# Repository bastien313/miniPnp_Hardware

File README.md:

# miniPnp_Hardware
hardware of mini PNP

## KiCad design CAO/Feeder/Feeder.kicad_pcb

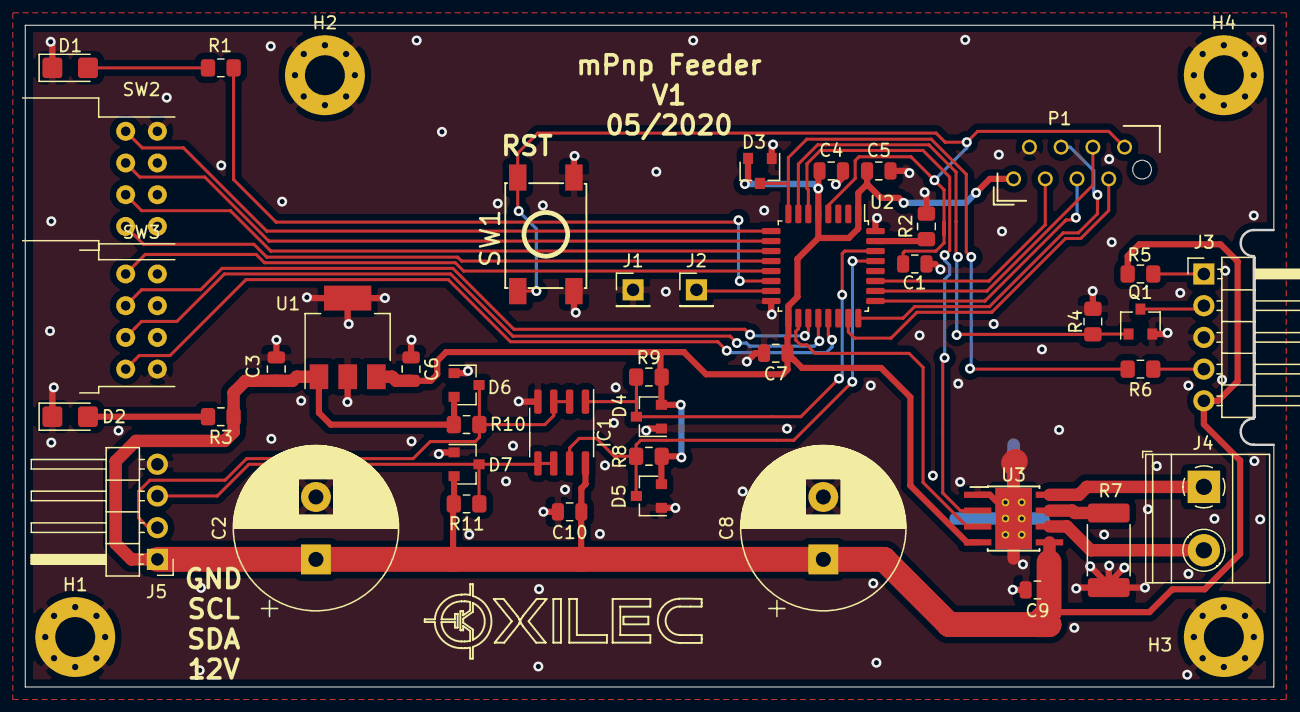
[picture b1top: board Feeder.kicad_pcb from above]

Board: 2 copper layers, 99.9 x 52.9 mm, 46 parts (0 on the bottom side), 36 nets.

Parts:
C1, C4, C5, C9, C10: 100nF; C_0805_2012Metric
C2, C8: 470uF 50V; CP_Radial_D13.0mm_P5.00mm
C3, C6: 330n 25V; C_0805_2012Metric
C7: 4.7uF 25V; C_0805_2012Metric
D1, D2: LED; LED_1206_3216Metric_Castellated
D3, D4, D5, D6, D7: BAT54S; SOT-23
H1, H2, H3, H4: MountingHole_Pad; MountingHole_3.2mm_M3_Pad_Via
IC1: PCA9600; SOIC-8_3.9x4.9mm_P1.27mm
J1, J2: Conn_01x01; PinHeader_1x01_P2.54mm_Vertical
J3: Conn_01x05; PinHeader_1x05_P2.54mm_Horizontal
J4: Born2; TerminalBlock_Phoenix_MKDS-1,5-2-5.08_1x02_P5.08mm_Horizont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
J5: Conn_01x04; PinHeader_1x04_P2.54mm_Horizontal
P1: CONN_4X2; 8Micro-MaTch
Q1: BSS138; SOT-23
R1, R3, R5, R8, R9, R10, R11: 1K; R_0805_2012Metric_Pad1.15x1.40mm_HandSolder
R2, R4: 100K; R_0805_2012Metric_Pad1.15x1.40mm_HandSolder
R6: 10k; R_0805_2012Metric_Pad1.15x1.40mm_HandSolder
R7: 0R; R_2512_6332Metric_Pad1.52x3.35mm_HandSolder
SW1: SW_Push; FSM2JSMA
SW2, SW3: SW_DIP_x04; DIPSW_4_COUDE
U1: MC33275ST-3.3T3G; SOT-223-3_TabPin2
U2: STM32F334K8Tx; LQFP-32_7x7mm_P0.8mm
U3: DRV8870DDA; Texas_HTSOP-8-1EP_3.9x4.9mm_P1.27mm_EP2.95x4.9mm_Mask2.4x3.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

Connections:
+3.3V: C4.1, C5.1, C6.2, C7.1, D3.2, D4.2, D5.2, P1.1, R8.1, R9.1, U1.3, U2.1, U2.5, U2.17, U3.4
+12V: C2.1, C3.2, C8.1, C9.1, C10.1, D6.2, D7.2, IC1.8, J3.5, J5.1, R3.1, R5.2, R10.1, R11.1, U1.1, U3.5
/ADR0: SW2.1, U2.9
/ADR1: SW2.2, U2.10
/ADR2: SW2.3, U2.11
/ADR3: SW2.4, U2.12
/ADR4: SW3.1, U2.13
/DC1: U2.18, U3.3
/DC2: U2.6, U3.2
/LEDIR_M: Q1.1, R4.2, U2.7
/NRST: C1.1, P1.8, SW1.1, U2.4
/SCL: D5.3, IC1.7, R8.2, U2.29
/SDA: D4.3, IC1.1, R9.2, U2.30
/TCK_SWCLK: P1.4, U2.24
/TDI: P1.5, U2.25
/TDO_SWO: P1.6, U2.26
/TIM15_CH1: D3.3, R6.2, U2.8
/TMS_SWDIO: P1.7, U2.23
/TRST: P1.3, U2.27
GND: C1.2, C2.2, C3.1, C4.2, C5.2, C6.1, C7.2, C8.2, C9.2, C10.2, D1.1, D2.1, D3.1, D4.1, D5.1, D6.1, D7.1, H1.1, H2.1, H3.1, H4.1, IC1.4, J1.1, J3.3, J5.4, P1.2, Q1.2, R2.2, R4.1, R7.2, SW1.2, SW2.5, SW2.6, SW2.7, SW2.8, SW3.5, SW3.6, SW3.7, SW3.8, U1.2, U2.16, U2.32, U3.1, U3.9
unnamed: D1.2, R1.2
unnamed: D2.2, R3.2
unnamed: D6.3, IC1.2, IC1.3, J5.2, R10.2
unnamed: D7.3, IC1.5, IC1.6, J5.3, R11.2
unnamed: J2.1, U2.15
unnamed: J3.1, R5.1
unnamed: J3.2, Q1.3
unnamed: J3.4, R6.1
unnamed: J4.1, U3.8
unnamed: J4.2, U3.6
unnamed: R1.1, U2.14
unnamed: R2.1, U2.31
unnamed: R7.1, U3.7
unnamed: SW3.2, U2.19
unnamed: SW3.3, U2.20
unnamed: SW3.4, U2.21

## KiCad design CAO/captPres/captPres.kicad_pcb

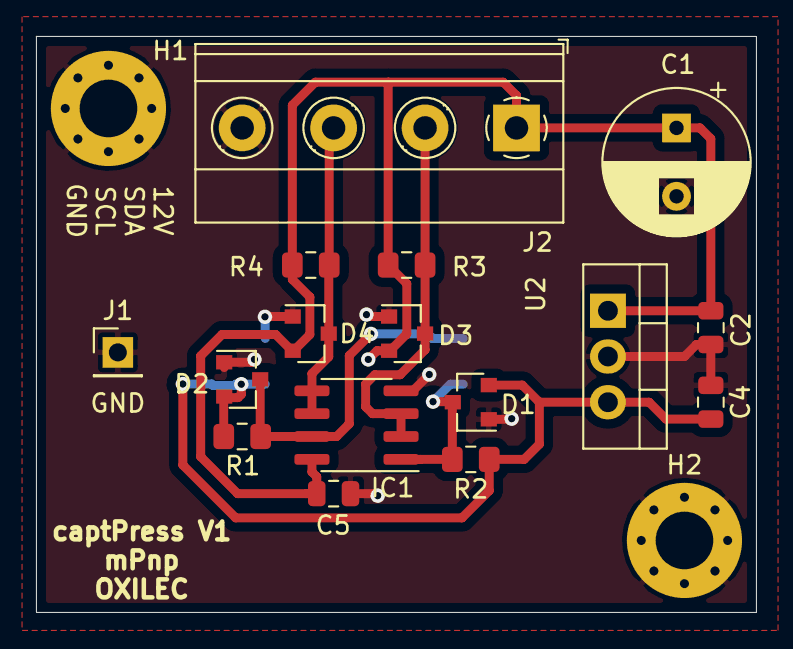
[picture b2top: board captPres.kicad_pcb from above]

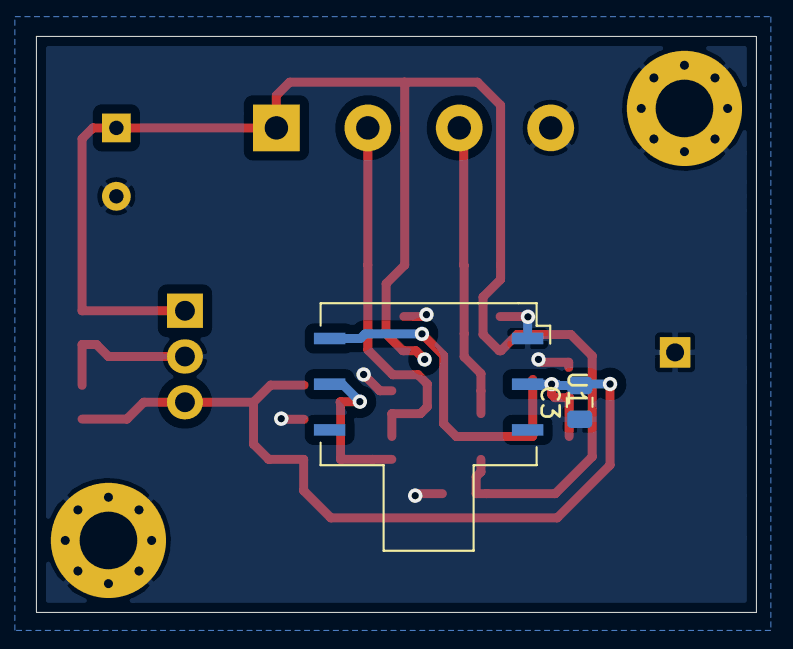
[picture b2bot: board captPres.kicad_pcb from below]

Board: 2 copper layers, 40.0 x 32.0 mm, 20 parts (2 on the bottom side), 7 nets.

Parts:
C1: CP1; CP_Radial_D8.0mm_P3.80mm
C2, C3, C5: 100nF; C_0805_2012Metric
C4: 2.2uF; C_0805_2012Metric
D1, D2, D3, D4: BAT54S; SOT-23
H1, H2: MountingHole_Pad; MountingHole_3.2mm_M3_Pad_Via
IC1: PCA9600; SOIC-8_3.9x4.9mm_P1.27mm
J1: Conn_01x01; PinHeader_1x01_P2.54mm_Vertical
J2: Conn_01x04; TerminalBlock_Phoenix_MKDS-1,5-4-5.08_1x04_P5.08mm_Horizont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
R1, R2, R3, R4: 1K; R_0805_2012Metric_Pad1.15x1.40mm_HandSolder
U1: ABPMRRV015PD2A3
U2: LF33_TO220; TO-220-3_Vertical

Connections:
+3V3USB: C3.2, C4.2, D1.2, D2.2, R1.1, R2.1, U1.2, U2.3
+12V: C1.1, C2.2, C5.1, D3.2, D4.2, IC1.8, J2.1, R3.1, R4.1, U2.1
/I2C/SCL: D2.3, IC1.7, R1.2, U1.6
/I2C/SDA: D1.3, IC1.1, R2.2, U1.5
GND: C1.2, C2.1, C3.1, C4.1, C5.2, D1.1, D2.1, D3.1, D4.1, H1.1, H2.1, IC1.4, J1.1, J2.4, U1.1, U2.2
unnamed: D3.3, IC1.2, IC1.3, J2.2, R3.2
unnamed: D4.3, IC1.5, IC1.6, J2.3, R4.2

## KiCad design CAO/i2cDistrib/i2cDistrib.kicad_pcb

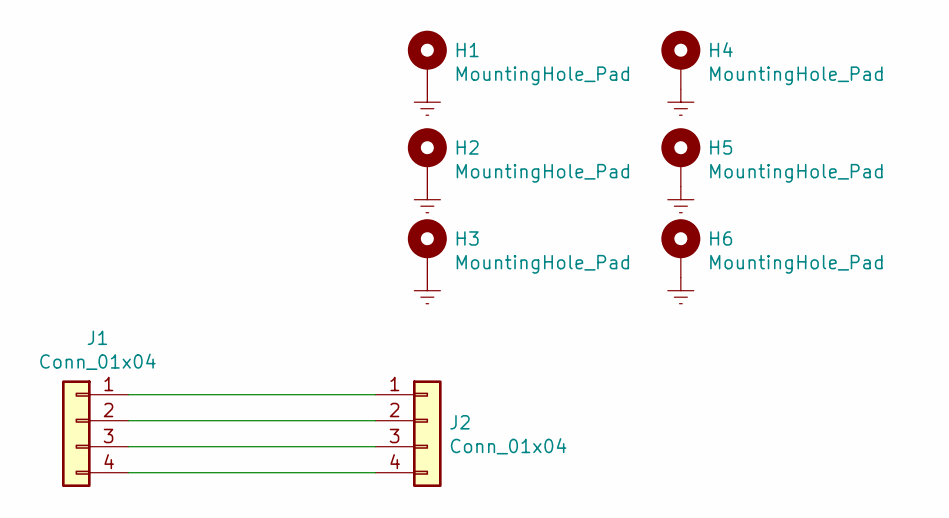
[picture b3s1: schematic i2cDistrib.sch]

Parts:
H1, H2, H3, H4, H5, H6: MountingHole_Pad; MountingHole_3mm_Pad_Via
J1, J2: Conn_01x04; Molex_KK-254_AE-6410-04A_1x04_P2.54mm_Vertical

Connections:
Earth: H1.1, H2.1, H3.1, H4.1, H5.1, H6.1
unnamed: J1.1, J2.1
unnamed: J1.2, J2.2
unnamed: J1.3, J2.3
unnamed: J1.4, J2.4

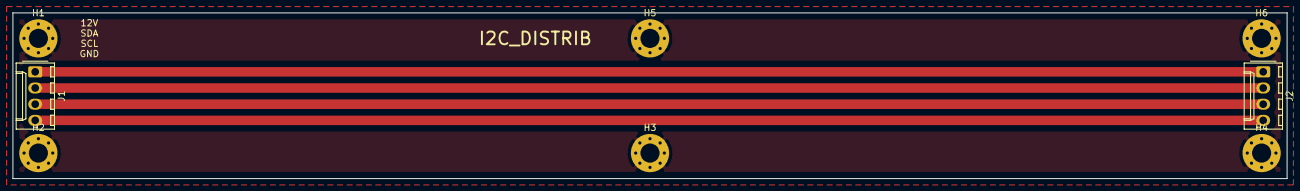
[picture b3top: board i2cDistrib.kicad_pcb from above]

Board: 2 copper layers, 200.0 x 26.0 mm, 8 parts (0 on the bottom side), 5 nets.

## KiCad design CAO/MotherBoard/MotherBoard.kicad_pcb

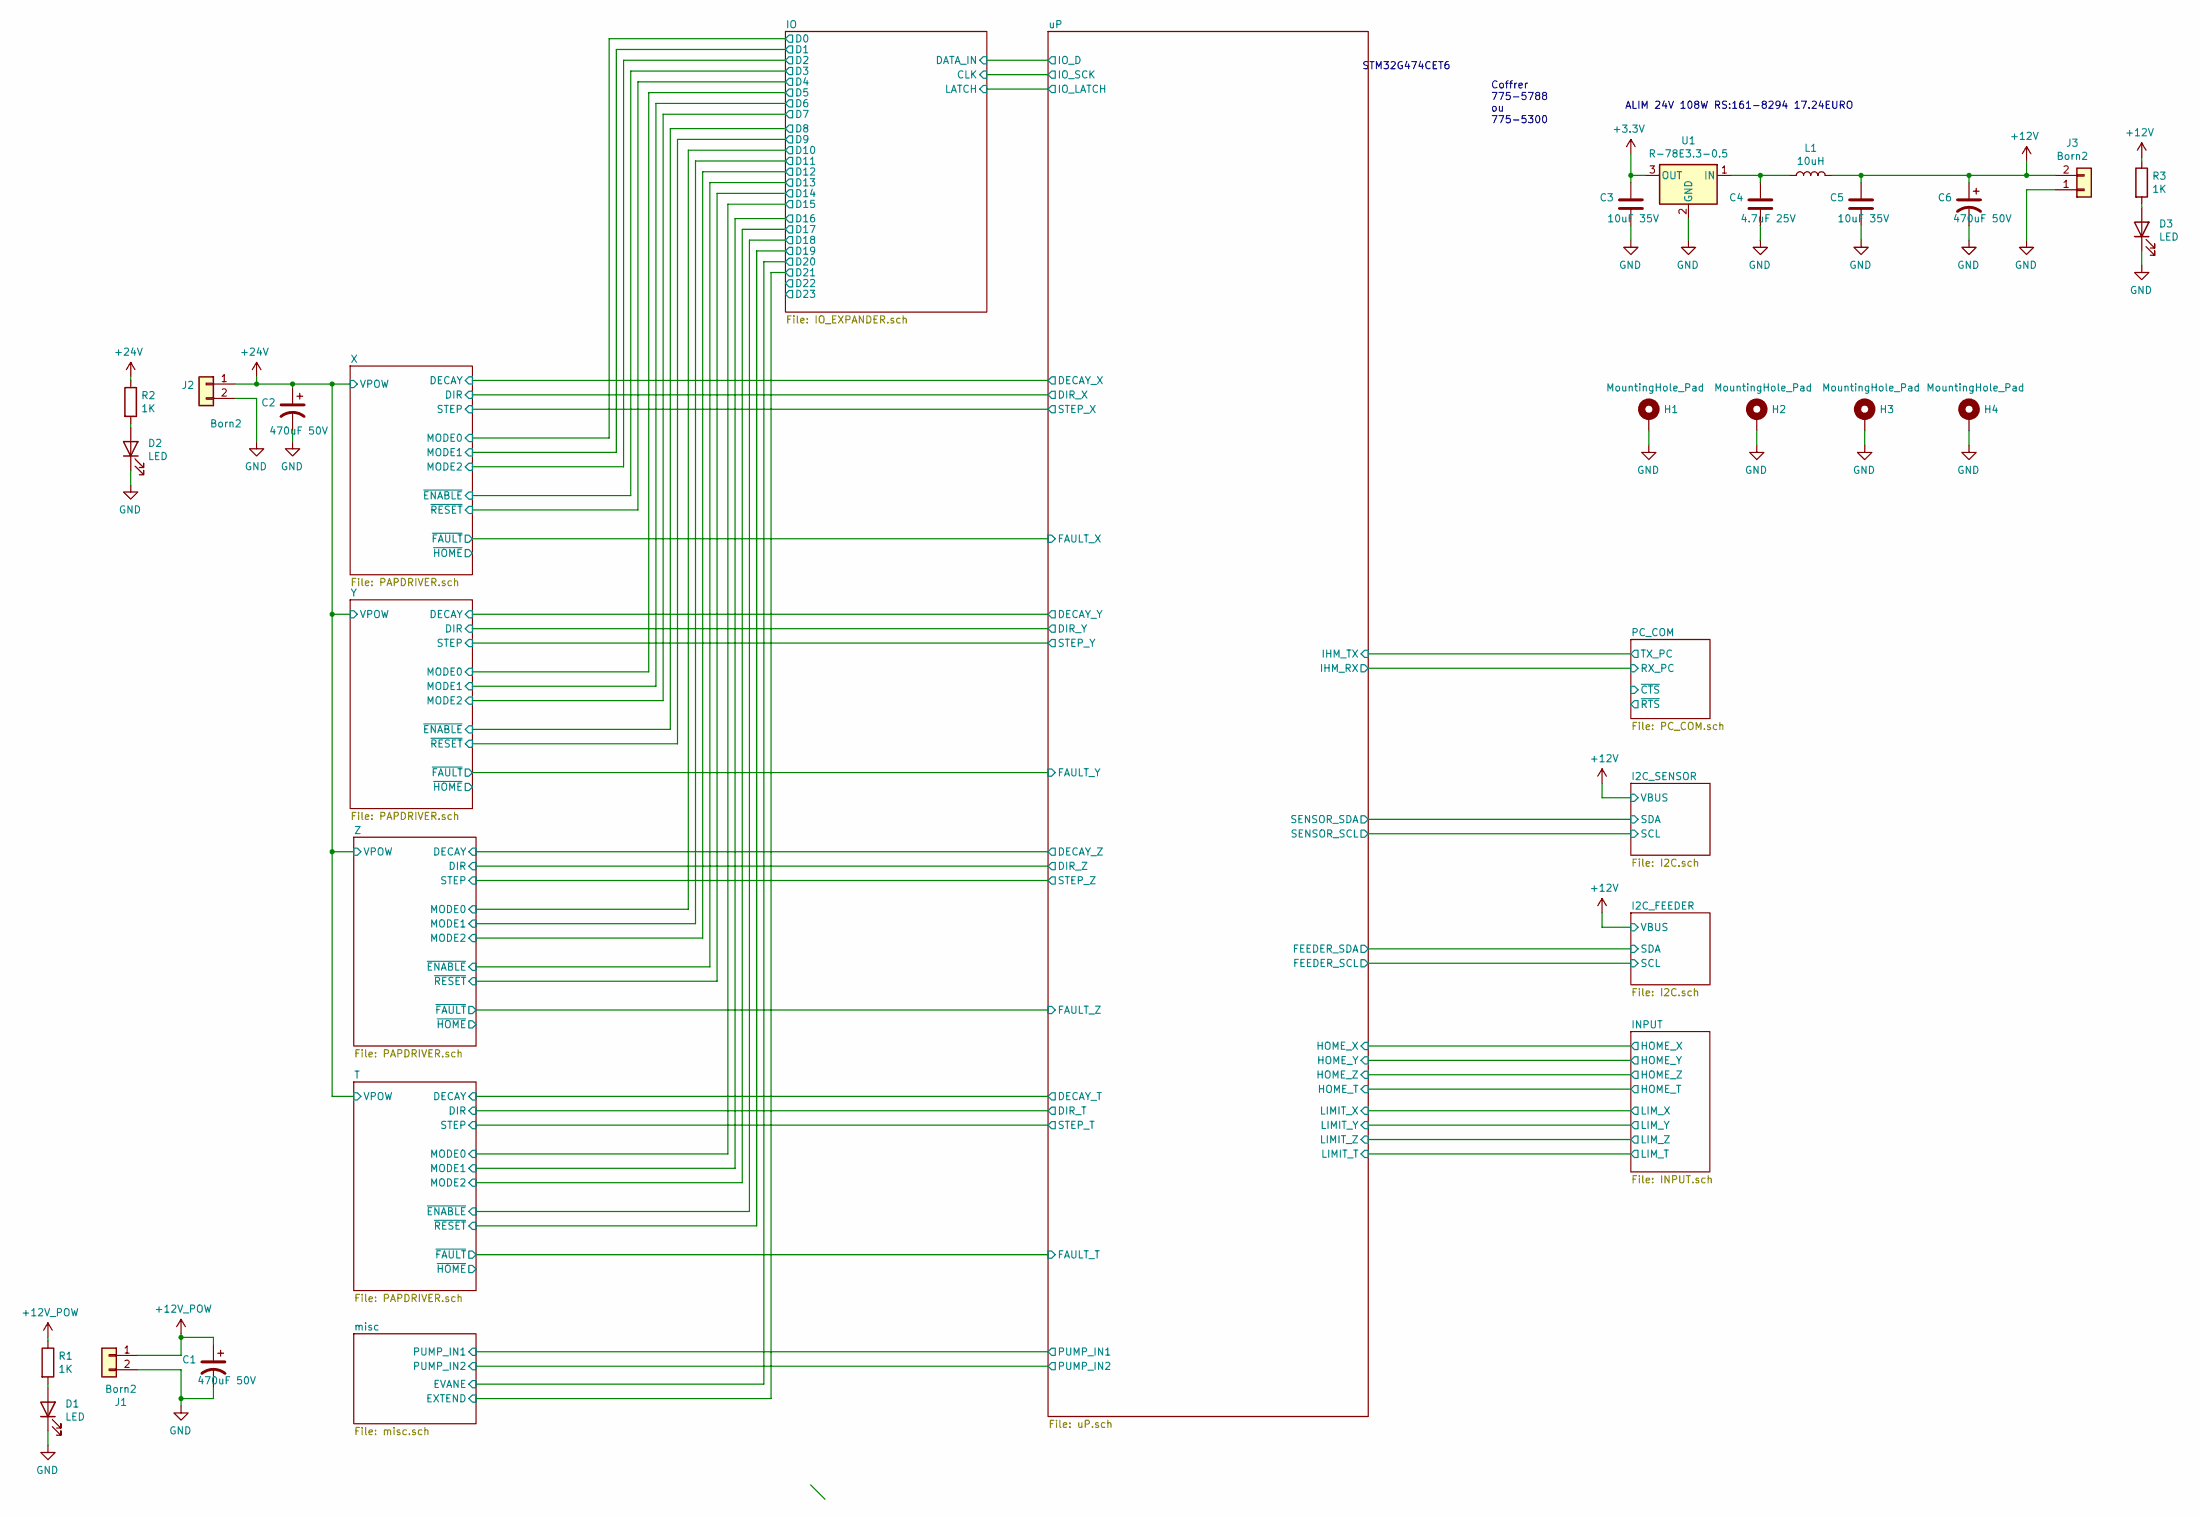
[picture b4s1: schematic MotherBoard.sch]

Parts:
C1, C2, C6: 470uF 50V; CP_Radial_D13.0mm_P5.00mm
C3, C5: 10uF 35V; C_1206_3216Metric
C4: 4.7uF 25V; C_0805_2012Metric
D1, D2, D3: LED; LED_1206_3216Metric_Castellated
H1, H2, H3, H4: MountingHole_Pad; MountingHole_3.2mm_M3_Pad_Via
J1, J2, J3: Born2; TerminalBlock_Phoenix_MKDS-1,5-2-5.08_1x02_P5.08mm_Horizont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
L1: 10uH; MCSD54-120MU
R1, R2, R3: 1K; R_0805_2012Metric_Pad1.15x1.40mm_HandSolder
U1: R-78E3.3-0.5; Converter_DCDC_RECOM_R-78E-0.5_THT

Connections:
+12V: C5.1, C6.1, J3.2, L1.1, R3.1; also elsewhere on the board
+12V_POW: C1.1, J1.1, R1.1; also elsewhere on the board
+24V: C2.1, J2.1, R2.1; also elsewhere on the board
unnamed: C4.1, L1.2, U1.1 (IN)
unnamed: D1.2 (A), R1.2
unnamed: D2.2 (A), R2.2
unnamed: D3.2 (A), R3.2

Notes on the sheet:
ALIM 24V 108W RS:161-8294 17.24EURO
STM32G474CET6
Coffrer 775-5788 ou 775-5300

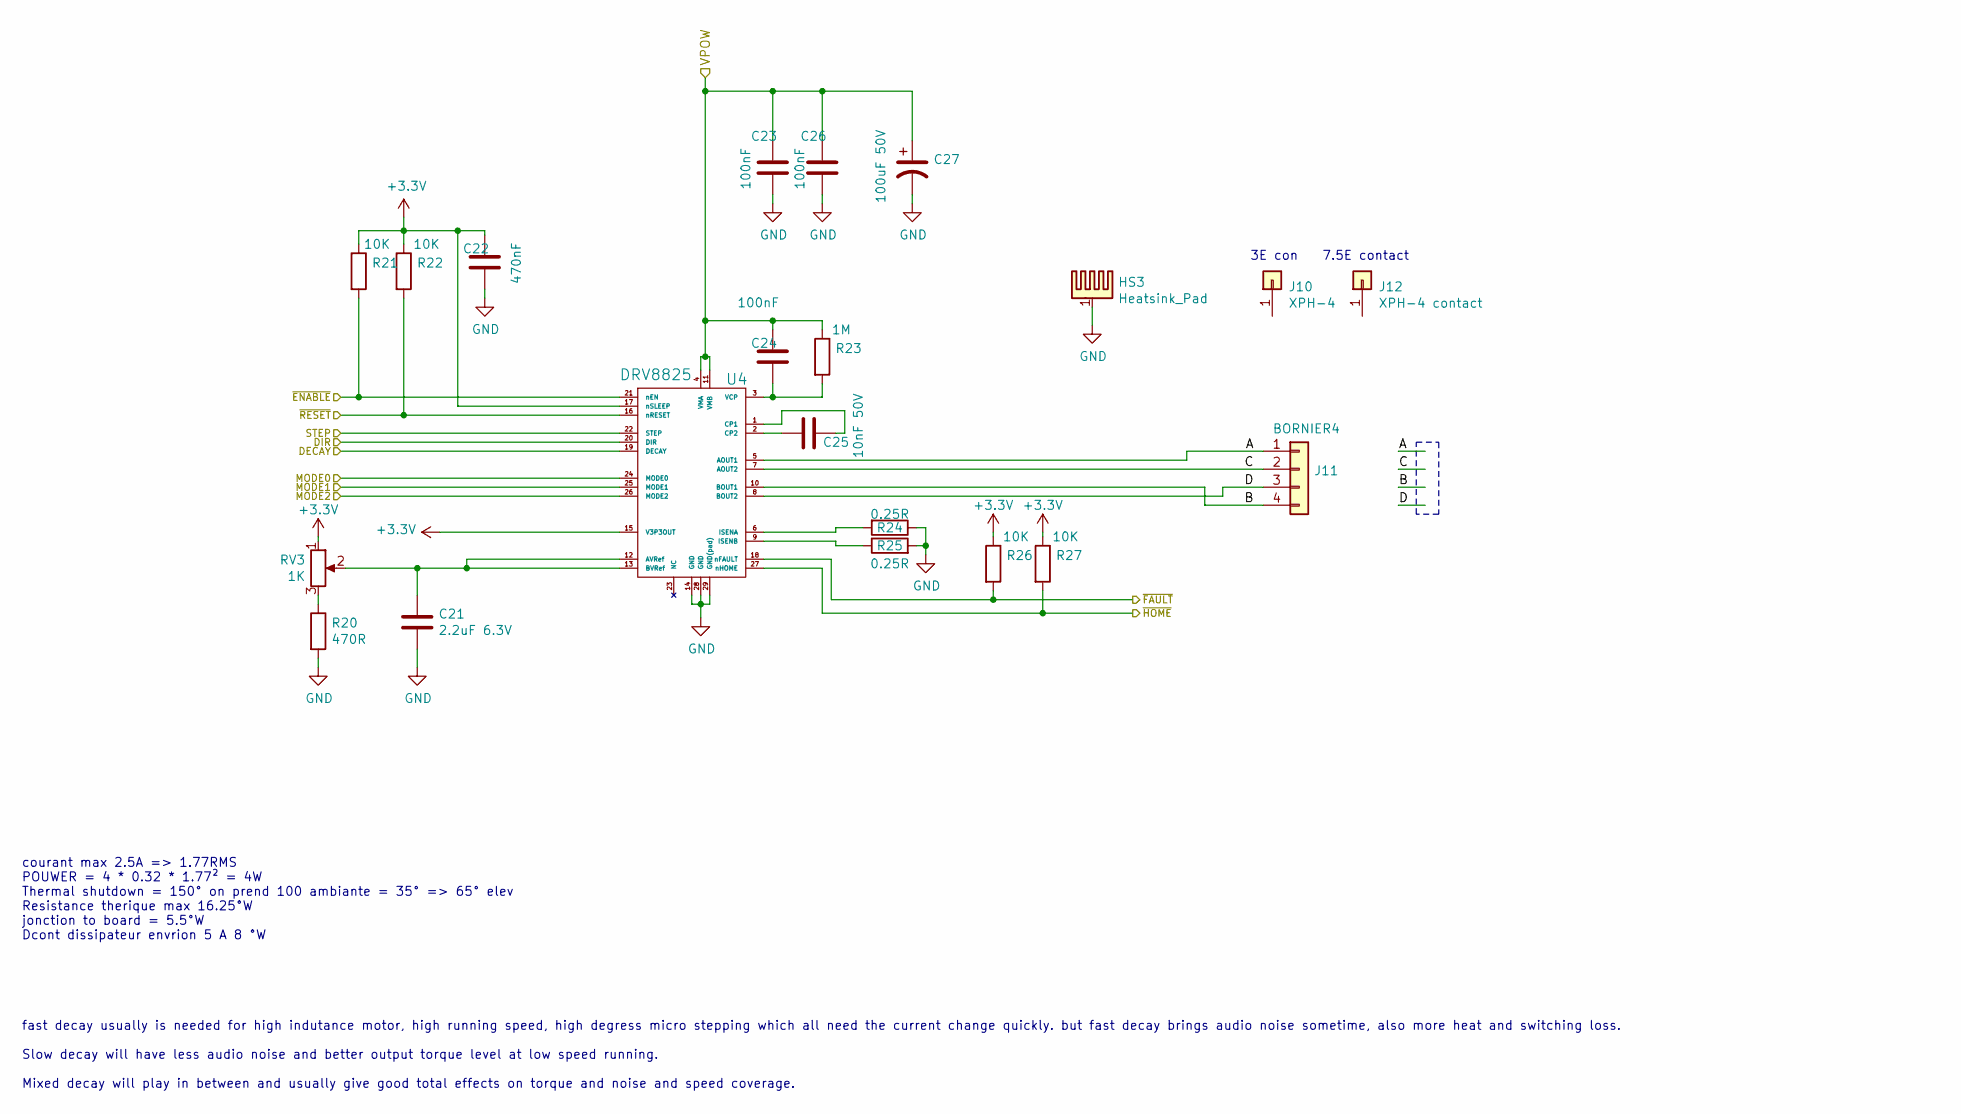
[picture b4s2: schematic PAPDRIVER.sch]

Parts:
C7: 2.2uF 6.3V; C_0805_2012Metric
C8: 470nF; C_0805_2012Metric
C9, C10, C12: 100nF; C_0805_2012Metric
C11: 10nF 50V; C_0805_2012Metric
C13: 100uF 50V; CP_Radial_D8.0mm_P3.80mm
HS1: Heatsink_Pad; BGA STD 115
J4: XPH-4; None
J5: BORNIER4; TerminalBlock_Phoenix_MKDS-1,5-4-5.08_1x04_P5.08mm_Horizont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
J6: XPH-4 contact; None
R4: 470R; R_0805_2012Metric_Pad1.15x1.40mm_HandSolder
R5, R6, R10, R11: 10K; R_0805_2012Metric_Pad1.15x1.40mm_HandSolder
R7: 1M; R_0805_2012Metric_Pad1.15x1.40mm_HandSolder
R8, R9: 0.25R; R_2512_6332Metric_Pad1.52x3.35mm_HandSolder
RV1: 1K; Potentiometer_Bourns_TC33X_Vertical
U2: DRV8825; HTSSOP-28-1EP_4.4x9.7mm_P0.65mm_EP3.4x9.5mm_ThermalVias

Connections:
+24V: C9.1, C10.1, C12.1, C13.1, R7.1, U2.4 (VMA), U2.11 (VMB); also elsewhere on the board
/IO/D0: U2.24 (MODE0); also elsewhere on the board
/IO/D1: U2.25 (MODE1); also elsewhere on the board
/IO/D2: U2.26 (MODE2); also elsewhere on the board
/IO/D3: R5.2, U2.21 (nEN); also elsewhere on the board
/IO/D4: R6.2, U2.16 (nRESET); also elsewhere on the board
/X/A: J5.1, U2.5 (AOUT1)
/X/B: J5.4, U2.10 (BOUT1)
/X/C: J5.2, U2.7 (AOUT2)
/X/D: J5.3, U2.8 (BOUT2)
/X/DECAY: U2.19 (DECAY); also elsewhere on the board
/X/DIR: U2.20 (DIR); also elsewhere on the board
/X/STEP: U2.22 (STEP); also elsewhere on the board
/X/~HOME~: R11.2, U2.27 (nHOME)
/uP/FAULT_X: R10.2, U2.18 (nFAULT); also elsewhere on the board
unnamed: C7.1, RV1.2, U2.12 (AVRef), U2.13 (BVRef)
unnamed: C10.2, R7.2, U2.3 (VCP)
unnamed: C11.1, U2.1 (CP1)
unnamed: C11.2, U2.2 (CP2)
unnamed: R4.1, RV1.3
unnamed: R8.2, U2.6 (ISENA)
unnamed: R9.1, U2.9 (ISENB)

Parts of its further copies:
C14, C21, C31: 2.2uF 6.3V; C_0805_2012Metric
C15, C22, C32: 470nF; C_0805_2012Metric
C16, C17, C19, C23, C24, C26, C33, C34, C36: 100nF; C_0805_2012Metric
C18, C25, C35: 10nF 50V; C_0805_2012Metric
C20, C27, C37: 100uF 50V; CP_Radial_D8.0mm_P3.80mm
HS2, HS3, HS4: Heatsink_Pad; BGA STD 115
J7, J10, J14: XPH-4; None
J8, J11, J15: BORNIER4; TerminalBlock_Phoenix_MKDS-1,5-4-5.08_1x04_P5.08mm_Horizont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
J9, J12, J16: XPH-4 contact; None
R12, R20, R34: 470R; R_0805_2012Metric_Pad1.15x1.40mm_HandSolder
R13, R14, R18, R19, R21, R22, R26, R27, R35, R36, R40, R41: 10K; R_0805_2012Metric_Pad1.15x1.40mm_HandSolder
R15, R23, R37: 1M; R_0805_2012Metric_Pad1.15x1.40mm_HandSolder
R16, R17, R24, R25, R38, R39: 0.25R; R_2512_6332Metric_Pad1.52x3.35mm_HandSolder
RV2, RV3, RV4: 1K; Potentiometer_Bourns_TC33X_Vertical
U3, U4, U6: DRV8825; HTSSOP-28-1EP_4.4x9.7mm_P0.65mm_EP3.4x9.5mm_ThermalVias

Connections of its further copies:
+24V: C16.1, C17.1, C19.1, C20.1, C23.1, C24.1, C26.1, C27.1, C33.1, C34.1, C36.1, C37.1, R15.1, R23.1, R37.1, U3.4 (VMA), U3.11 (VMB), U4.4 (VMA), U4.11 (VMB), U6.4 (VMA), U6.11 (VMB); also elsewhere on the board
/IO/D5: U3.24 (MODE0); also elsewhere on the board
/IO/D6: U3.25 (MODE1); also elsewhere on the board
/IO/D7: U3.26 (MODE2); also elsewhere on the board
/IO/D8: R13.2, U3.21 (nEN); also elsewhere on the board
/IO/D9: R14.2, U3.16 (nRESET); also elsewhere on the board
/IO/D10: U4.24 (MODE0); also elsewhere on the board
/IO/D11: U4.25 (MODE1); also elsewhere on the board
/IO/D12: U4.26 (MODE2); also elsewhere on the board
/IO/D13: R21.2, U4.21 (nEN); also elsewhere on the board
/IO/D14: R22.2, U4.16 (nRESET); also elsewhere on the board
/IO/D15: U6.24 (MODE0); also elsewhere on the board
/IO/D16: U6.25 (MODE1); also elsewhere on the board
/IO/D17: U6.26 (MODE2); also elsewhere on the board
/IO/D18: R35.2, U6.21 (nEN); also elsewhere on the board
/IO/D19: R36.2, U6.16 (nRESET); also elsewhere on the board
/T/A: J15.1, U6.5 (AOUT1)
/T/B: J15.4, U6.10 (BOUT1)
/T/C: J15.2, U6.7 (AOUT2)
/T/D: J15.3, U6.8 (BOUT2)
/T/DECAY: U6.19 (DECAY); also elsewhere on the board
/T/DIR: U6.20 (DIR); also elsewhere on the board
/T/STEP: U6.22 (STEP); also elsewhere on the board
/T/~HOME~: R41.2, U6.27 (nHOME)
/Y/A: J8.1, U3.5 (AOUT1)
/Y/B: J8.4, U3.10 (BOUT1)
/Y/C: J8.2, U3.7 (AOUT2)
/Y/D: J8.3, U3.8 (BOUT2)
/Y/DECAY: U3.19 (DECAY); also elsewhere on the board
/Y/DIR: U3.20 (DIR); also elsewhere on the board
/Y/STEP: U3.22 (STEP); also elsewhere on the board
/Y/~HOME~: R19.2, U3.27 (nHOME)
/Z/A: J11.1, U4.5 (AOUT1)
/Z/B: J11.4, U4.10 (BOUT1)
/Z/C: J11.2, U4.7 (AOUT2)
/Z/D: J11.3, U4.8 (BOUT2)
/Z/DECAY: U4.19 (DECAY); also elsewhere on the board
/Z/DIR: U4.20 (DIR); also elsewhere on the board
/Z/STEP: U4.22 (STEP); also elsewhere on the board
/Z/~HOME~: R27.2, U4.27 (nHOME)
/uP/FAULT_T: R40.2, U6.18 (nFAULT); also elsewhere on the board
/uP/FAULT_Y: R18.2, U3.18 (nFAULT); also elsewhere on the board
/uP/FAULT_Z: R26.2, U4.18 (nFAULT); also elsewhere on the board
unnamed: C14.1, RV2.2, U3.12 (AVRef), U3.13 (BVRef)
unnamed: C17.2, R15.2, U3.3 (VCP)
unnamed: C18.1, U3.1 (CP1)
unnamed: C18.2, U3.2 (CP2)
unnamed: C21.1, RV3.2, U4.12 (AVRef), U4.13 (BVRef)
unnamed: C24.2, R23.2, U4.3 (VCP)
unnamed: C25.1, U4.1 (CP1)
unnamed: C25.2, U4.2 (CP2)
unnamed: C31.1, RV4.2, U6.12 (AVRef), U6.13 (BVRef)
unnamed: C34.2, R37.2, U6.3 (VCP)
unnamed: C35.1, U6.1 (CP1)
unnamed: C35.2, U6.2 (CP2)
unnamed: R12.1, RV2.3
unnamed: R16.2, U3.6 (ISENA)
unnamed: R17.1, U3.9 (ISENB)
unnamed: R20.1, RV3.3
unnamed: R24.2, U4.6 (ISENA)
unnamed: R25.1, U4.9 (ISENB)
unnamed: R34.1, RV4.3
unnamed: R38.2, U6.6 (ISENA)
unnamed: R39.1, U6.9 (ISENB)

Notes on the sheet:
courant max 2.5A => 1.77RMS POUWER = 4 * 0.32 * 1.77² = 4W Thermal shutdown = 150° on prend 100 ambiante = 35° => 65° elev Resistance therique max 16.25°W jonction to board = 5.5°W Dcont dissipateur envrion 5 A 8 °W
7.5E contact
3E con
fast decay usually is needed for high indutance motor, high running speed, high degress micro stepping which all need the current change quickly. but fast decay brings audio noise sometime, also more heat and switching loss. Slow decay will have less audio noise and better output torque level at lo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

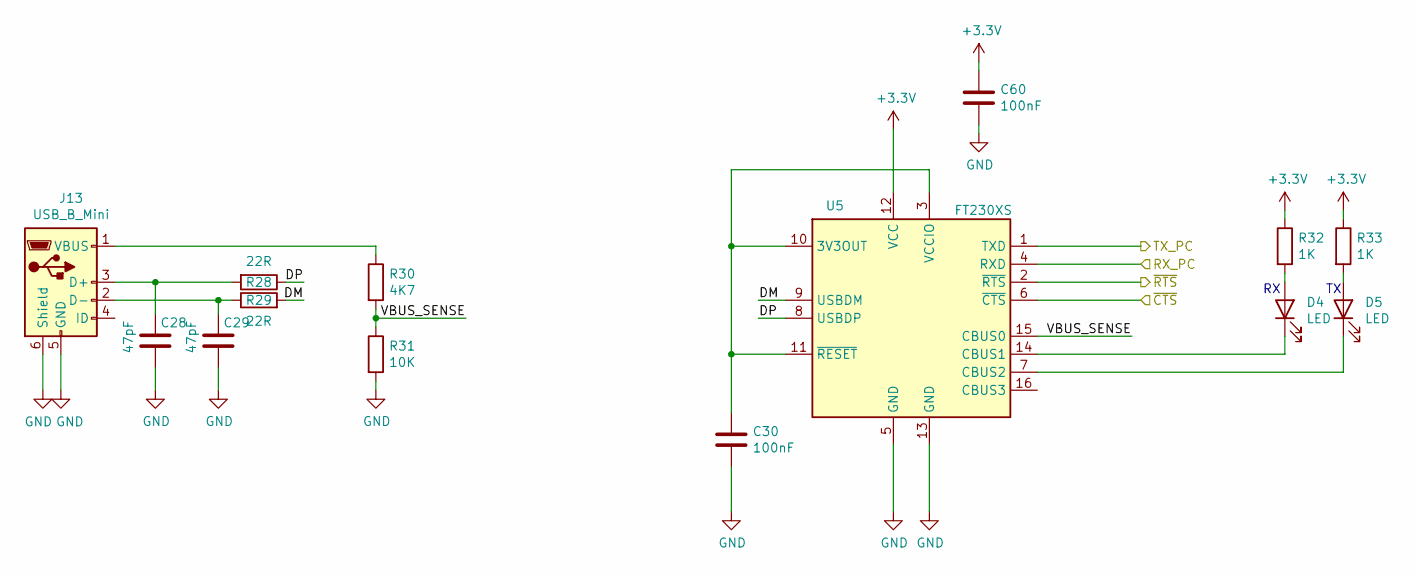
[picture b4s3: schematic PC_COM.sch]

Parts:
C28, C29: 47pF; C_0805_2012Metric
C30, C60: 100nF; C_0805_2012Metric
D4, D5: LED; LED_1206_3216Metric_Castellated
J13: USB_B_Mini; USB_Mini-B_Lumberg_2486_01_Horizontal
R28, R29: 22R; R_0805_2012Metric_Pad1.15x1.40mm_HandSolder
R30: 4K7; R_0805_2012Metric_Pad1.15x1.40mm_HandSolder
R31: 10K; R_0805_2012Metric_Pad1.15x1.40mm_HandSolder
R32, R33: 1K; R_0805_2012Metric_Pad1.15x1.40mm_HandSolder
U5: FT230XS; SSOP-16_3.9x4.9mm_P0.635mm

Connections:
/PC_COM/DM: R29.2, U5.9 (USBDM)
/PC_COM/DP: R28.1, U5.8 (USBDP)
/PC_COM/VBUS_SENSE: R30.2, R31.1, U5.15 (CBUS0)
/PC_COM/~CTS~: U5.6 (~CTS)
/PC_COM/~RTS~: U5.2 (~RTS)
/uP/IHM_RX: U5.4 (RXD); also elsewhere on the board
/uP/IHM_TX: U5.1 (TXD); also elsewhere on the board
unnamed: C28.1, J13.3 (D+), R28.2
unnamed: C29.1, J13.2 (D-), R29.1
unnamed: C30.1, U5.3 (VCCIO), U5.10 (3V3OUT), U5.11 (~RESET)
unnamed: D4.1 (K), U5.14 (CBUS1)
unnamed: D4.2 (A), R32.2
unnamed: D5.1 (K), U5.7 (CBUS2)
unnamed: D5.2 (A), R33.2
unnamed: J13.1 (VBUS), R30.1

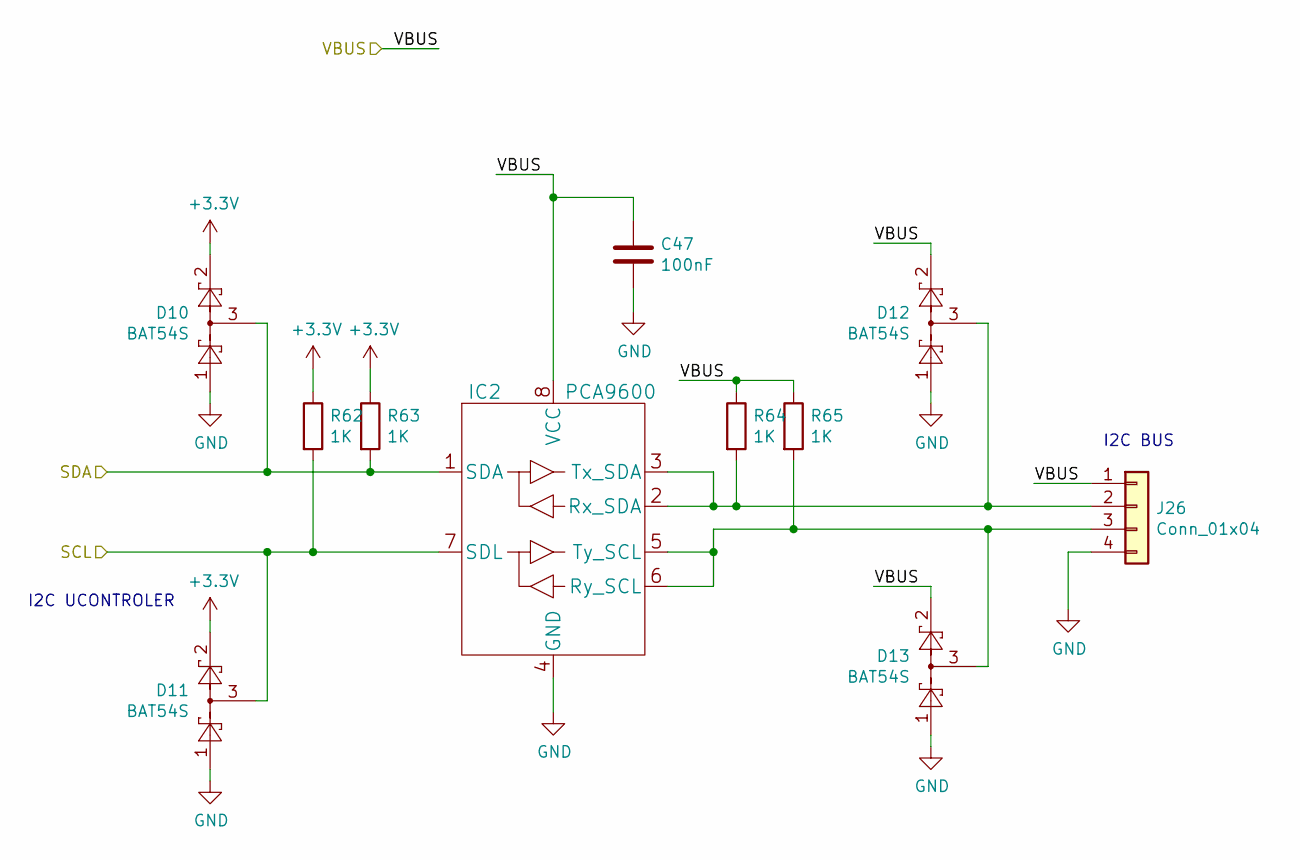
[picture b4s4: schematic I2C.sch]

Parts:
C38: 100nF; C_0805_2012Metric
D6, D7, D8, D9: BAT54S; SOT-23
IC1: PCA9600; SOIC-8_3.9x4.9mm_P1.27mm
J17: Conn_01x04; TerminalBlock_Phoenix_MKDS-1,5-4-5.08_1x04_P5.08mm_Horizont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
R42, R43, R44, R45: 1K; R_0805_2012Metric_Pad1.15x1.40mm_HandSolder

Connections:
+12V: C38.1, D8.2, D9.2, IC1.8 (VCC), J17.1, R44.1, R45.1; also elsewhere on the board
/uP/FEEDER_SCL: D7.3, IC1.7 (SDL), R42.2; also elsewhere on the board
/uP/FEEDER_SDA: D6.3, IC1.1 (SDA), R43.2; also elsewhere on the board
unnamed: D8.3, IC1.2 (Rx_SDA), IC1.3 (Tx_SDA), J17.2, R44.2
unnamed: D9.3, IC1.5 (Ty_SCL), IC1.6 (Ry_SCL), J17.3, R45.2

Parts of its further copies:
C47: 100nF; C_0805_2012Metric
D10, D11, D12, D13: BAT54S; SOT-23
IC2: PCA9600; SOIC-8_3.9x4.9mm_P1.27mm
J26: Conn_01x04; TerminalBlock_Phoenix_MKDS-1,5-4-5.08_1x04_P5.08mm_Horizont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
R62, R63, R64, R65: 1K; R_0805_2012Metric_Pad1.15x1.40mm_HandSolder

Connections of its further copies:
+12V: C47.1, D12.2, D13.2, IC2.8 (VCC), J26.1, R64.1, R65.1; also elsewhere on the board
/I2C_SENSOR/SCL: D11.3, IC2.7 (SDL), R62.2; also elsewhere on the board
/I2C_SENSOR/SDA: D10.3, IC2.1 (SDA), R63.2; also elsewhere on the board
unnamed: D12.3, IC2.2 (Rx_SDA), IC2.3 (Tx_SDA), J26.2, R64.2
unnamed: D13.3, IC2.5 (Ty_SCL), IC2.6 (Ry_SCL), J26.3, R65.2

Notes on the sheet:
I2C UCONTROLER
I2C BUS

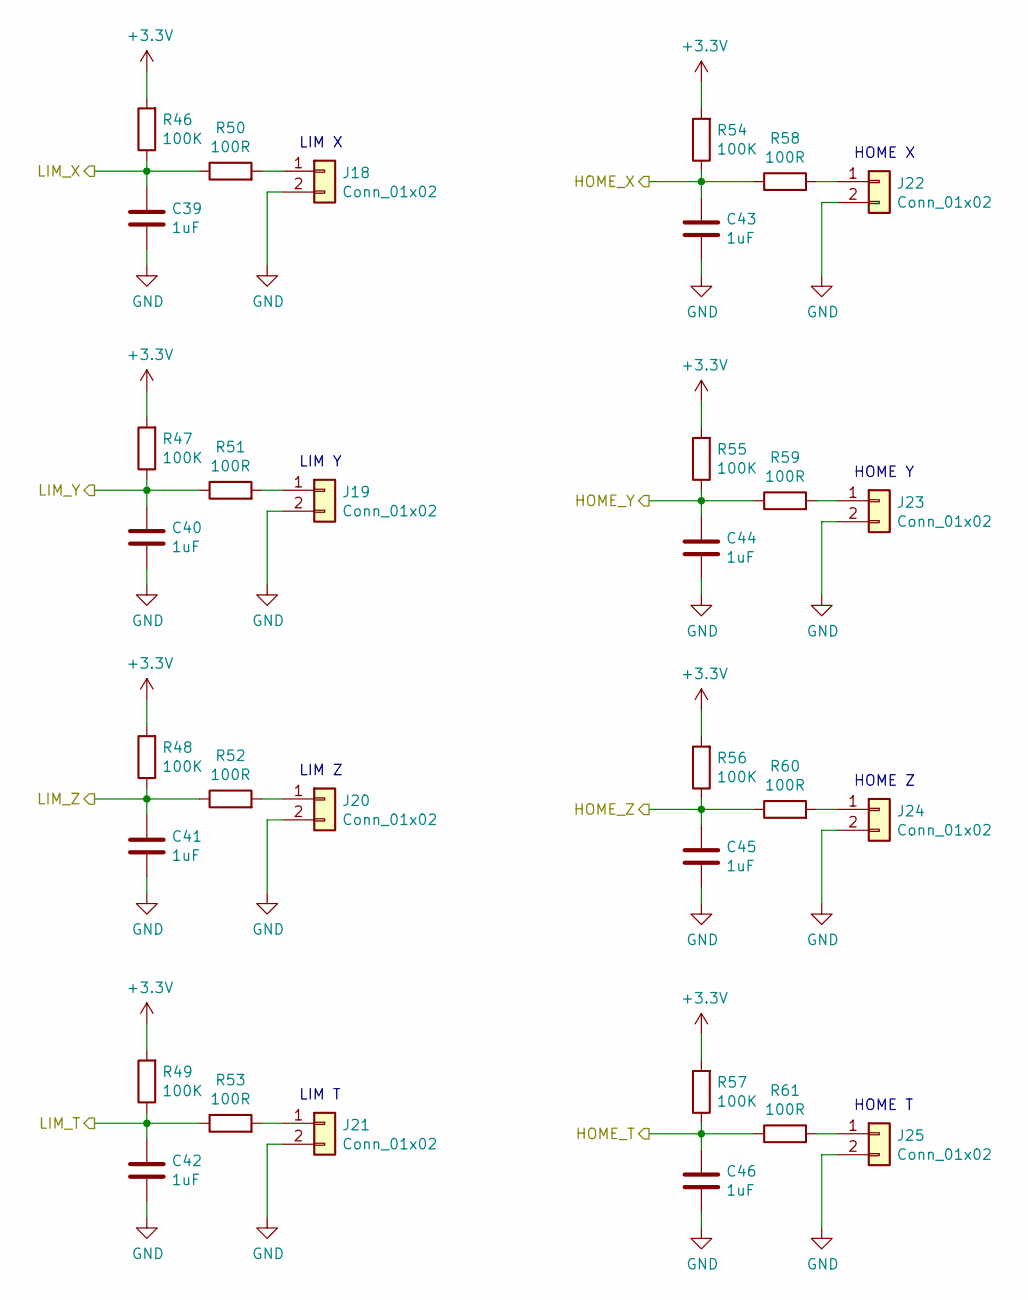
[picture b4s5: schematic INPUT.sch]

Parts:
C39, C40, C41, C42, C43, C44, C45, C46: 1uF; C_0805_2012Metric
J18, J19, J20, J21, J22, J23, J24, J25: Conn_01x02; TerminalBlock_Phoenix_MKDS-1,5-2-5.08_1x02_P5.08mm_Horizont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
R46, R47, R48, R49, R54, R55, R56, R57: 100K; R_0805_2012Metric_Pad1.15x1.40mm_HandSolder
R50, R51, R52, R53, R58, R59, R60, R61: 100R; R_0805_2012Metric_Pad1.15x1.40mm_HandSolder

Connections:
/INPUT/HOME_T: C46.1, R57.1, R61.1; also elsewhere on the board
/INPUT/HOME_X: C43.1, R54.1, R58.1; also elsewhere on the board
/uP/LIMIT_T: C42.1, R49.1, R53.1; also elsewhere on the board
/uP/LIMIT_X: C39.1, R46.1, R50.1; also elsewhere on the board
/uP/LIMIT_Y: C40.1, R47.1, R51.1; also elsewhere on the board
/uP/LIMIT_Z: C41.1, R48.1, R52.1; also elsewhere on the board
unnamed: J18.1, R50.2
unnamed: J19.1, R51.2
unnamed: J20.1, R52.2
unnamed: J21.1, R53.2
unnamed: J22.1, R58.2
unnamed: J23.1, R59.2
unnamed: J24.1, R60.2
unnamed: J25.1, R61.2

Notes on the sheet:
HOME X
HOME Y
HOME Z
LIM X
LIM Y
LIM Z
HOME T
LIM T

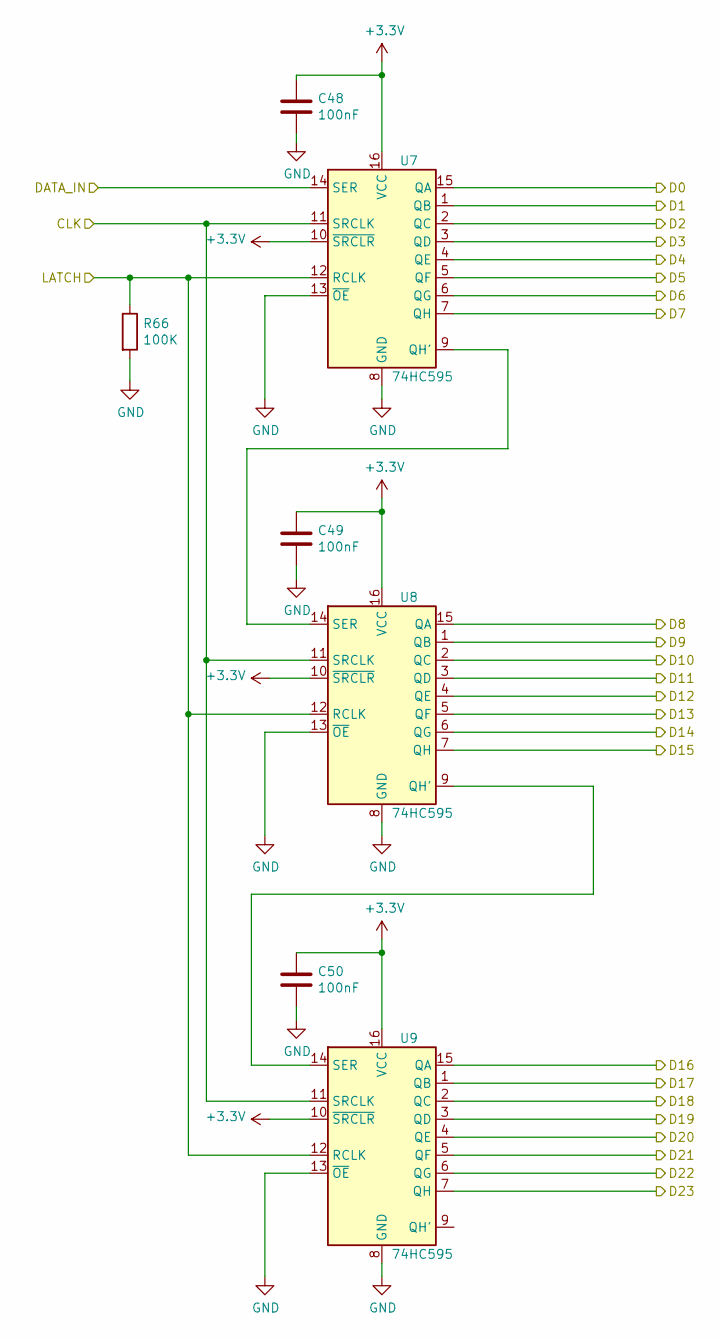
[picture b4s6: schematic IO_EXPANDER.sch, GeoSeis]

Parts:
C44, C45, C50: 100nF; C_0805_2012Metric
R66: 100K; R_0805_2012Metric_Pad1.15x1.40mm_HandSolder
U7, U8, U9: 74HC595; SOIC-16_3.9x9.9mm_P1.27mm

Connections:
/IO/CLK: U7.11 (SRCLK), U8.11 (SRCLK), U9.11 (SRCLK); also elsewhere on the board
/IO/D0: U7.15 (QA); also elsewhere on the board
/IO/D1: U7.1 (QB); also elsewhere on the board
/IO/D2: U7.2 (QC); also elsewhere on the board
/IO/D3: U7.3 (QD); also elsewhere on the board
/IO/D4: U7.4 (QE); also elsewhere on the board
/IO/D5: U7.5 (QF); also elsewhere on the board
/IO/D6: U7.6 (QG); also elsewhere on the board
/IO/D7: U7.7 (QH); also elsewhere on the board
/IO/D8: U8.15 (QA); also elsewhere on the board
/IO/D9: U8.1 (QB); also elsewhere on the board
/IO/D10: U8.2 (QC); also elsewhere on the board
/IO/D11: U8.3 (QD); also elsewhere on the board
/IO/D12: U8.4 (QE); also elsewhere on the board
/IO/D13: U8.5 (QF); also elsewhere on the board
/IO/D14: U8.6 (QG); also elsewhere on the board
/IO/D15: U8.7 (QH); also elsewhere on the board
/IO/D16: U9.15 (QA); also elsewhere on the board
/IO/D17: U9.1 (QB); also elsewhere on the board
/IO/D18: U9.2 (QC); also elsewhere on the board
/IO/D19: U9.3 (QD); also elsewhere on the board
/IO/D20: U9.4 (QE); also elsewhere on the board
/IO/D21: U9.5 (QF); also elsewhere on the board
/IO/D22: U9.6 (QG)
/IO/D23: U9.7 (QH)
/IO/DATA_IN: U7.14 (SER); also elsewhere on the board
/uP/IO_LATCH: R66.1, U7.12 (RCLK), U8.12 (RCLK), U9.12 (RCLK); also elsewhere on the board
unnamed: U7.9 (QH'), U8.14 (SER)
unnamed: U8.9 (QH'), U9.14 (SER)

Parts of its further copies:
C48, C49: 100nF; C_0805_2012Metric
